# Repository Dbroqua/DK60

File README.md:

# Projet déplacé vers [framagit](https://framagit.org/mechkeyboards/DK60)

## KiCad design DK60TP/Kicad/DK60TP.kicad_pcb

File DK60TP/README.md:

# DK60TP

## About

## Electronic parts
* 1x [ATMEGA32U4](https://www.digikey.com/product-detail/en/microchip-technology/ATMEGA32U4-AUR/ATMEGA32U4-AURCT-ND/3440960)
* 1x [SER3686CT](https://www.digikey.com/product-detail/en/epson/FA-238-16.0000MB-C3/SER3686CT-ND/2403459)
* 2x [22pF capacitors](https://www.digikey.com/product-detail/en/kemet/C0805C220J5GACTU/399-1113-1-ND/411388)
* 9x [0.1uF capacitors](https://www.digikey.com/product-detail/en/yageo/CC0805ZRY5V9BB104/311-1361-1-ND/2103145)
* 1x [4.7uF capacitor](https://www.digikey.com/product-detail/en/murata-electronics-north-america/GRM21BR61E475KA12L/490-3335-1-ND/702876)
* 1x [1uF capacitor](https://www.digikey.com/product-detail/en/yageo/CC0805KKX7R7BB105/311-1365-1-ND/2103149)
* 1x [2.2uF capacitor](https://www.digikey.com/product-detail/en/yageo/CC0805KKX7R7BB225/311-1881-1-ND/5195783)
* 2x [10uF capacitor](https://www.digikey.com/product-detail/en/yageo/CC1206KKX7R7BB106/311-1956-1-ND/5195858)
* 62x [1N4148WTPMSCT](https://www.digikey.com/product-detail/en/micro-commercial-co/1N4148W-TP/1N4148WTPMSCT-ND/717311)
* 5x [WS2812B (only one pack)](http://www.mouser.fr/ProductDetail/Seeed-Studio/110990053/?qs=sGAEpiMZZMtzPgOfznR9QTO1l8g3oIgjmGvsDAmgJrQ%3d)
* 1x [Mini USB connector](https://www.digikey.com/product-detail/en/hirose-electric-co-ltd/UX60SC-MB-5S8/H11589CT-ND/1949225)
* 1x [Inductor 4.7µH](https://www.digikey.com/product-detail/en/bourns-inc/SRN4018-4R7M/SRN4018-4R7MCT-ND/3821520)
* 1x [PLCC 2835](https://www.digikey.com/product-detail/en/osram-opto-semiconductors-inc/LY-T68F-T2V2-35-1-Z/475-2835-1-ND/2176372)
* 1x [Pin header 2x5 angled](https://www.digikey.com/product-detail/en/harwin-inc/M22-2540505/952-2141-ND/3728105)
* 2x [10k Ohm resistors](https://www.digikey.com/product-detail/en/stackpole-electronics-inc/RMCF0805JT10K0/RMCF0805JT10K0CT-ND/1942577)
* 2x [22 Ohm resistors](https://www.digikey.com/product-detail/en/stackpole-electronics-inc/RMCF0805JT22R0/RMCF0805JT22R0CT-ND/1942533)
* 1x [620 Ohm resistor](https://www.digikey.fr/product-detail/fr/stackpole-electronics-inc/RMCF0603JT620R/RMCF0603JT620RCT-ND/1943168)
* 1x [0.5 Ohm resistor](https://www.digikey.com/product-detail/en/yageo/RL0805FR-7W0R5L/311-.5LUCT-ND/3885461)
* 1x [100k Ohm resistor](https://www.digikey.com/product-detail/en/stackpole-electronics-inc/RMCF0805JT100K/RMCF0805JT100KCT-ND/1942592)
* 2x [4.7k Ohm resistor](https://www.digikey.com/product-detail/en/stackpole-electronics-inc/RMCF0805JT4K70/RMCF0805JT4K70CT-ND/1942570)
* 1x [Button](https://www.digikey.com/product-detail/en/e-switch/TL3342F160QG-TR/EG2531CT-ND/379004)
* 1x [PAM2804](https://www.arrow.com/en/products/pam2804aab010/diodes-incorporated)

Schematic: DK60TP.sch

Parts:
C1, C2: 22p; C_0805_HandSoldering
C3, C4, C5, C6: 0.1u; C_0805_HandSoldering
C7: 4.7u; C_0805_HandSoldering
C8: 1u; C_0805_HandSoldering
J1: USB_mini_micro_B; USB_miniB_hirose_5S8
M1, M2, M3, M4: MISC; BreakHoles
P1: CONN_02X04; Molex_PicoBlade_53048-1010_10x1.25mm_Angled
R1, R2: 10K; R_0805_HandSoldering
R3, R4: 22; R_0805_HandSoldering
SW1: SW_PUSH; SW_SPST_TL3342
U0: ATMEGA32U4; TQFP-44_10x10mm_Pitch0.8mm
X1: XTAL_GND; FA-238

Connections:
BACKLIT: U0.12 (PB7/~RTS); also elsewhere on the board
CAPS_LED: U0.1 (PE6/AIN0); also elsewhere on the board
Col0: U0.36 (PF7); also elsewhere on the board
Col1: U0.38 (PF5); also elsewhere on the board
Col2: U0.39 (PF4); also elsewhere on the board
Col3: P1.3, U0.40 (PF1); also elsewhere on the board
Col4: P1.4, U0.30 (PB6); also elsewhere on the board
Col5: P1.5, U0.9 (PB1/SCK); also elsewhere on the board
Col6: U0.26 (T1/PD6); also elsewhere on the board
Col7: U0.11 (PB3/MISO); also elsewhere on the board
Col8: U0.25 (ICP1/PD4); also elsewhere on the board
Col9: U0.28 (PB4); also elsewhere on the board
ColA: U0.21 (PD3/TXD1); also elsewhere on the board
ColB: U0.19 (PD1/INT1); also elsewhere on the board
ColC: U0.18 (PD0/INT0); also elsewhere on the board
ColD: U0.8 (PB0/SS); also elsewhere on the board
D2: P1.7, U0.20 (PD2/RXD1)
D5: P1.6, U0.22 (PD5/XCK1)
DOUT: P1.10; also elsewhere on the board
GND: C1.2, C2.2, C3.2, C4.2, C5.2, C6.2, C7.2, C8.2, J1.5 (GND), J1.6 (SHIELD), P1.2, R2.1, SW1.1, U0.5 (UGnd), U0.15 (GND), U0.23 (GND), U0.35 (GND), U0.43 (GND); also elsewhere on the board
unnamed: C8.1, U0.6 (UCap)
unnamed: J1.2 (D-), R3.2
unnamed: J1.3 (D+), R4.1
unnamed: R2.2, U0.33 (~HWB/PE2)
unnamed: R3.1, U0.3 (D-)
unnamed: R4.2, U0.4 (D+)
RESET: R1.2, SW1.2, U0.13 (~RESET)
RGB: U0.27 (T0/PD7); also elsewhere on the board
Row0: U0.37 (PF6); also elsewhere on the board
Row1: U0.31 (PC6); also elsewhere on the board
Row2: U0.29 (PB5); also elsewhere on the board
Row3: U0.10 (PB2/MOSI); also elsewhere on the board
Row4: P1.8, U0.32 (PC7); also elsewhere on the board
VCC: C3.1, C4.1, C5.1, C6.1, C7.1, J1.1 (VUSB), P1.1, R1.1, U0.2 (UVcc), U0.7 (VBus), U0.14 (VCC), U0.24 (AVCC), U0.34 (VCC), U0.44 (AVCC); also elsewhere on the board
XTAL1: C1.1, U0.16 (XTAL1), X1.1
XTAL2: C2.1, U0.17 (XTAL2), X1.2

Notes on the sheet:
External sheets
Power decoupling
Reset
Clock
µControler
Split PCB holes
Trackpoint connector

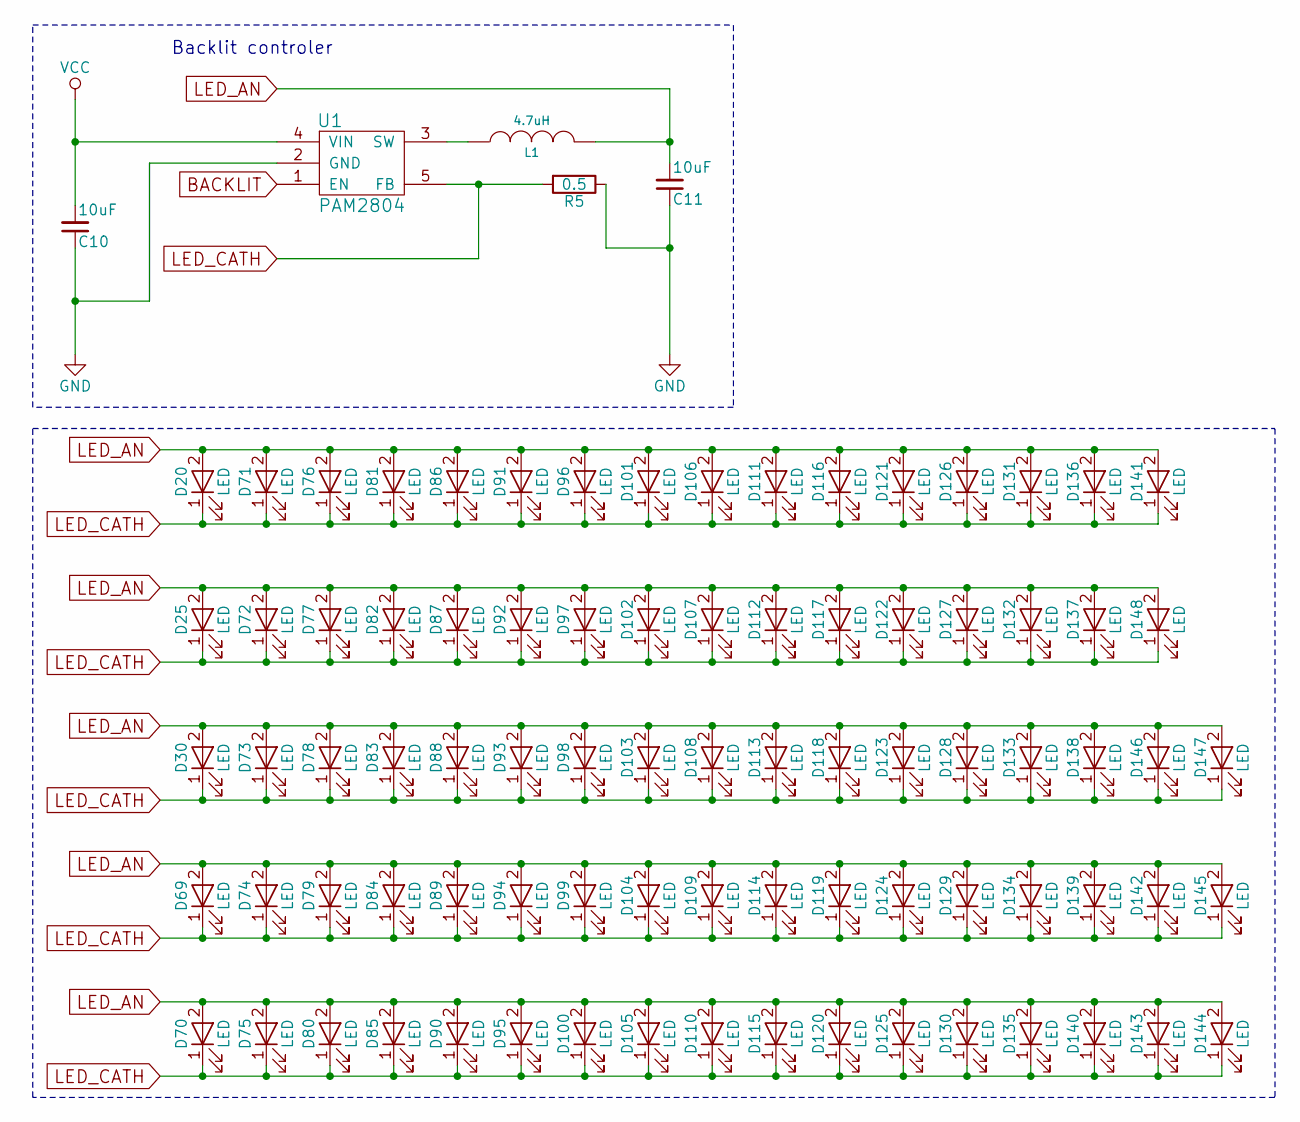
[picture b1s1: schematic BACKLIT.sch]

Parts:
C10, C11: 10uF; C_0805_HandSoldering
D20, D25, D30, D69, D70, D71, D72, D73, D74, D75, D76, D77, D78, D79, D80, D81, D82, D83, D84, D85, D86, D87, D88, D89, D90, D91, D92, D93, D94, D95, D96, D97, D98, D99, D100, D101, D102, D103, D104, D105, D106, D107, D108, D109, D110, D111, D112, D113, D114, D115, D116, D117, D118, D119, D120, D121, D122, D123, D124, D125, D126, D127, D128, D129, D130, D131, D132, D133, D134, D135, D136, D137, D138, D139, D140, D141, D142, D143, D144, D145, D146, D147, D148: LED; LED_TH_BIVAR
L1: 4.7uH; Inductor_Bourn_4mmx4mm
R5: 0.5; R_0805_HandSoldering
U1: PAM2804; SOT-23-5

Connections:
BACKLIT: U1.1 (EN); also elsewhere on the board
GND: C10.1, C11.1, R5.1, U1.2 (GND); also elsewhere on the board
LED_AN: C11.2, D20.2 (A), D25.2 (A), D30.2 (A), D69.2 (A), D70.2 (A), D71.2 (A), D72.2 (A), D73.2 (A), D74.2 (A), D75.2 (A), D76.2 (A), D77.2 (A), D78.2 (A), D79.2 (A), D80.2 (A), D81.2 (A), D82.2 (A), D83.2 (A), D84.2 (A), D85.2 (A), D86.2 (A), D87.2 (A), D88.2 (A), D89.2 (A), D90.2 (A), D91.2 (A), D92.2 (A), D93.2 (A), D94.2 (A), D95.2 (A), D96.2 (A), D97.2 (A), D98.2 (A), D99.2 (A), D100.2 (A), D101.2 (A), D102.2 (A), D103.2 (A), D104.2 (A), D105.2 (A), D106.2 (A), D107.2 (A), D108.2 (A), D109.2 (A), D110.2 (A), D111.2 (A), D112.2 (A), D113.2 (A), D114.2 (A), D115.2 (A), D116.2 (A), D117.2 (A), D118.2 (A), D119.2 (A), D120.2 (A), D121.2 (A), D122.2 (A), D123.2 (A), D124.2 (A), D125.2 (A), D126.2 (A), D127.2 (A), D128.2 (A), D129.2 (A), D130.2 (A), D131.2 (A), D132.2 (A), D133.2 (A), D134.2 (A), D135.2 (A), D136.2 (A), D137.2 (A), D138.2 (A), D139.2 (A), D140.2 (A), D141.2 (A), D142.2 (A), D143.2 (A), D144.2 (A), D145.2 (A), D146.2 (A), D147.2 (A), D148.2 (A), L1.2
LED_CATH: D20.1 (K), D25.1 (K), D30.1 (K), D69.1 (K), D70.1 (K), D71.1 (K), D72.1 (K), D73.1 (K), D74.1 (K), D75.1 (K), D76.1 (K), D77.1 (K), D78.1 (K), D79.1 (K), D80.1 (K), D81.1 (K), D82.1 (K), D83.1 (K), D84.1 (K), D85.1 (K), D86.1 (K), D87.1 (K), D88.1 (K), D89.1 (K), D90.1 (K), D91.1 (K), D92.1 (K), D93.1 (K), D94.1 (K), D95.1 (K), D96.1 (K), D97.1 (K), D98.1 (K), D99.1 (K), D100.1 (K), D101.1 (K), D102.1 (K), D103.1 (K), D104.1 (K), D105.1 (K), D106.1 (K), D107.1 (K), D108.1 (K), D109.1 (K), D110.1 (K), D111.1 (K), D112.1 (K), D113.1 (K), D114.1 (K), D115.1 (K), D116.1 (K), D117.1 (K), D118.1 (K), D119.1 (K), D120.1 (K), D121.1 (K), D122.1 (K), D123.1 (K), D124.1 (K), D125.1 (K), D126.1 (K), D127.1 (K), D128.1 (K), D129.1 (K), D130.1 (K), D131.1 (K), D132.1 (K), D133.1 (K), D134.1 (K), D135.1 (K), D136.1 (K), D137.1 (K), D138.1 (K), D139.1 (K), D140.1 (K), D141.1 (K), D142.1 (K), D143.1 (K), D144.1 (K), D145.1 (K), D146.1 (K), D147.1 (K), D148.1 (K), R5.2, U1.5 (FB)
unnamed: L1.1, U1.3 (SW)
VCC: C10.2, U1.4 (VIN); also elsewhere on the board

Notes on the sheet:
Backlit controler

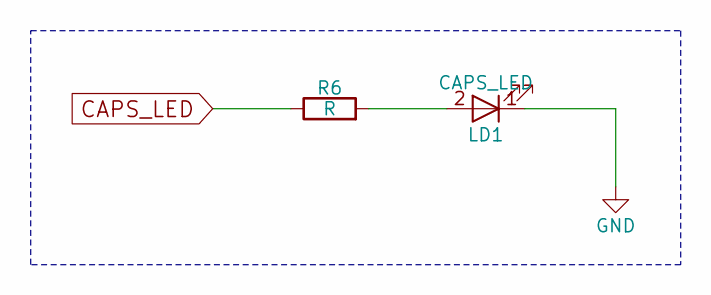
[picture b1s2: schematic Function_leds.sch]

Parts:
LD1: CAPS_LED; LED_PLCC_2835
R6: R; R_0805_HandSoldering

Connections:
CAPS_LED: R6.1; also elsewhere on the board
GND: LD1.1 (K); also elsewhere on the board
unnamed: LD1.2 (A), R6.2

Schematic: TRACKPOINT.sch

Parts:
C9: 2.2u; C_0805_HandSoldering
C17, C18, C19: 0.1u; C_0805_HandSoldering
D154, D155, D156: WS2812B
DM34, DM44, DM54: D; D_SOD123
KM340: LMB; Mx_100
KM341, KM541: KEYSW; Mx_125
KM440: MMB; Mx_100
KM540: KEYSW; Mx_100
P2: MAIN_BOARD; Molex_PicoBlade_53048-1010_10x1.25mm_Angled
P3: TRACKPOINT; Molex_PicoBlade_53048-0510_05x1.25mm_Angled
R7, R8: 4.7K; R_0805_HandSoldering
R9: 100K; R_0805_HandSoldering

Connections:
/TRACKPOINT/Col3: KM340.1, KM341.1, P2.3
/TRACKPOINT/Col4: KM440.1, P2.4
/TRACKPOINT/Col5: KM540.1, KM541.1, P2.5
/TRACKPOINT/D2: P2.7, P3.3, R8.2
/TRACKPOINT/D5: P2.6, P3.5, R7.2
/TRACKPOINT/RGB: D154.4 (DIN), P2.10
/TRACKPOINT/Row4: DM34.1 (K), DM44.1 (K), DM54.1 (K), P2.8
GND: C17.2, C18.2, C19.2, D154.3 (VSS), D155.3 (VSS), D156.3 (VSS), P2.2, P3.2, R9.2; also elsewhere on the board
unnamed: C9.1, P3.4, R9.1
unnamed: D154.2 (DOUT), D155.4 (DIN)
unnamed: D155.2 (DOUT), D156.4 (DIN)
unnamed: DM34.2 (A), KM340.2, KM341.2
unnamed: DM44.2 (A), KM440.2
unnamed: DM54.2 (A), KM540.2, KM541.2
VCC: C9.2, C17.1, C18.1, C19.1, D154.1 (VDD), D155.1 (VDD), D156.1 (VDD), P2.1, P3.1, R7.1, R8.1; also elsewhere on the board

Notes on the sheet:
Connector
Buttons
Trackpoint

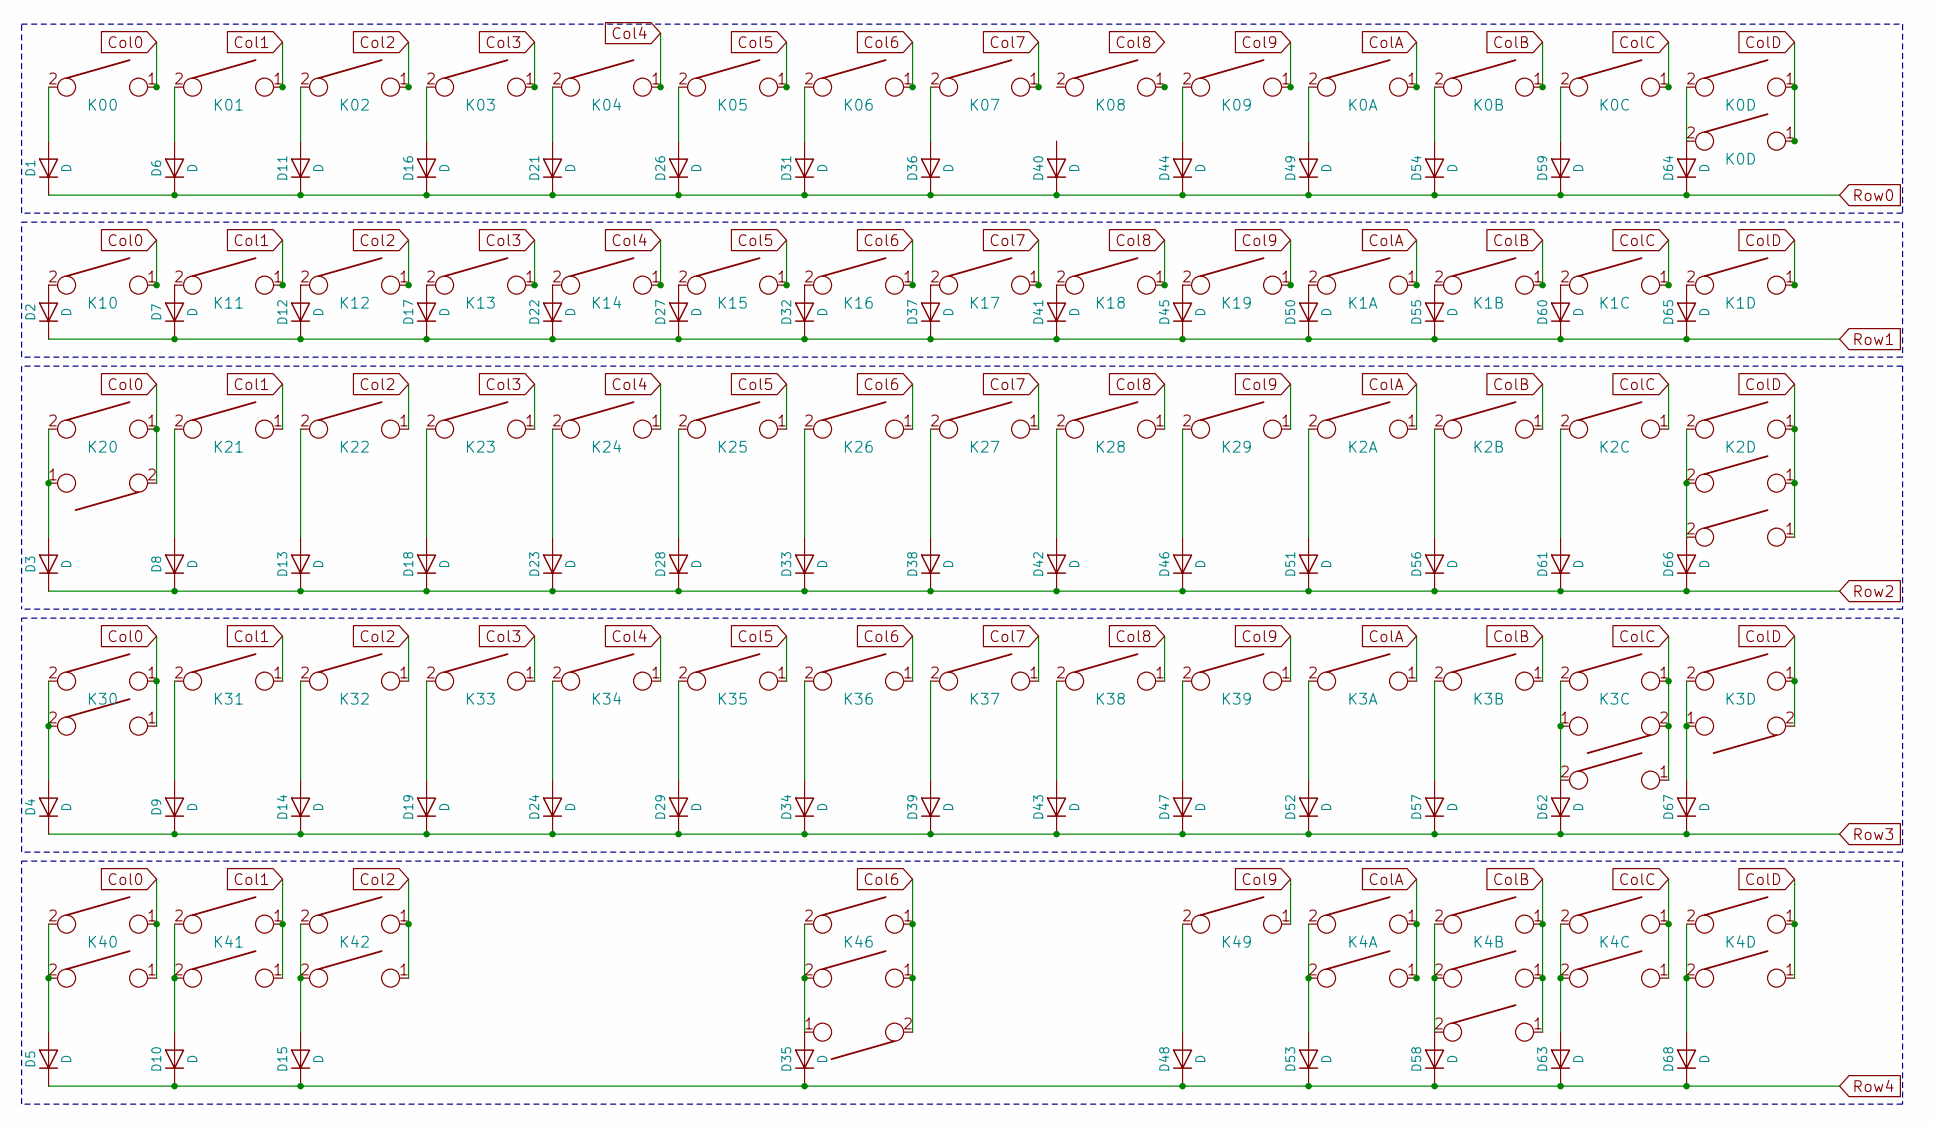
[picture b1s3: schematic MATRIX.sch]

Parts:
D1, D2, D3, D4, D5, D6, D7, D8, D9, D10, D11, D12, D13, D14, D15, D16, D17, D18, D19, D21, D22, D23, D24, D26, D27, D28, D29, D31, D32, D33, D34, D35, D36, D37, D38, D39, D40, D41, D42, D43, D44, D45, D46, D47, D48, D49, D50, D51, D52, D53, D54, D55, D56, D57, D58, D59, D60, D61, D62, D63, D64, D65, D66, D67, D68: D; D_SOD123
K1: K00; Mx_100
K2: K10; Mx_150
K3: K20; Mx_175
K4: K20; Mx_175_STEPPED
K5: K30; Mx_225
K6: K30; Mx_125
K7: K40; Mx_125
K8: K40; Mx_150
K9: K01; Mx_100
K10: K11; Mx_100
K11: K21; Mx_100
K12: K31; Mx_100
K13: K41; Mx_125
K14: K41; Mx_100
K15: K02; Mx_100
K16: K12; Mx_100
K17: K22; Mx_100
K18: K32; Mx_100
K19: K42; Mx_125
K20: K42; Mx_150
K21: K03; Mx_100
K22: K13; Mx_100
K23: K23; Mx_100
K24: K33; Mx_100
K25: K2D; Mx_125
K26: K3D; Mx_175
K27: K04; Mx_100
K28: K14; Mx_100
K29: K24; Mx_100
K30: K34; Mx_100
K31: K3C; Mx_100
K32: K05; Mx_100
K33: K15; Mx_100
K34: K25; Mx_100
K35: K35; Mx_100
K38: K06; Mx_100
K39: K16; Mx_100
K40: K26; Mx_100
K41: K36; Mx_100
K42: K46; Mx_600
K44: K46; Mx_625
K45: K46; Mx_700
K46: K07; Mx_100
K47: K17; Mx_100
K48: K27; Mx_100
K49: K37; Mx_100
K50: K08; Mx_100
K51: K18; Mx_100
K52: K28; Mx_100
K53: K38; Mx_100
K54: K09; Mx_100
K55: K19; Mx_100
K56: K29; Mx_100
K57: K39; Mx_100
K58: K49; Mx_100
K59: K0A; Mx_100
K60: K1A; Mx_100
K61: K2A; Mx_100
K62: K3A; Mx_100
K63: K4A; Mx_125
K64: K4A; Mx_150
K65: K0B; Mx_100
K66: K1B; Mx_100
K67: K2B; Mx_100
K68: K3B; Mx_100
K69: K4B; Mx_100
K70: K4B; Mx_125
K71: K4B; Mx_150
K72: K0C; Mx_100
K73: K1C; Mx_100
K74: K2C; Mx_100
K75: K3C; Mx_275
K76: K4C; Mx_100
K77: K4C; Mx_125
K78: K0D; Mx_100
K79: K0D; Mx_200
K80: K1D; Mx_150
K81: K2D; Mx_225
K82: K2D; Mx_200
K83: K3D; Mx_100
K84: K3C; Mx_175
K85: K4D; Mx_125
K86: K4D; Mx_150

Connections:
Col0: K1.1, K2.1, K3.1, K4.2, K5.1, K6.1, K7.1, K8.1; also elsewhere on the board
Col1: K9.1, K10.1, K11.1, K12.1, K13.1, K14.1; also elsewhere on the board
Col2: K15.1, K16.1, K17.1, K18.1, K19.1, K20.1; also elsewhere on the board
Col3: K21.1, K22.1, K23.1, K24.1; also elsewhere on the board
Col4: K27.1, K28.1, K29.1, K30.1; also elsewhere on the board
Col5: K32.1, K33.1, K34.1, K35.1; also elsewhere on the board
Col6: K38.1, K39.1, K40.1, K41.1, K42.1, K44.1, K45.2; also elsewhere on the board
Col7: K46.1, K47.1, K48.1, K49.1; also elsewhere on the board
Col8: K51.1, K52.1, K53.1; also elsewhere on the board
Col9: K54.1, K55.1, K56.1, K57.1, K58.1; also elsewhere on the board
ColA: K59.1, K60.1, K61.1, K62.1, K63.1, K64.1; also elsewhere on the board
ColB: K65.1, K66.1, K67.1, K68.1, K69.1, K70.1, K71.1; also elsewhere on the board
ColC: K31.2, K72.1, K73.1, K74.1, K75.1, K76.1, K77.1, K84.1; also elsewhere on the board
ColD: K25.1, K26.2, K78.1, K79.1, K80.1, K81.1, K82.1, K83.1, K85.1, K86.1; also elsewhere on the board
unnamed: D1.2 (A), K1.2
unnamed: D2.2 (A), K2.2
unnamed: D3.2 (A), K3.2, K4.1
unnamed: D4.2 (A), K5.2, K6.2
unnamed: D5.2 (A), K7.2, K8.2
unnamed: D6.2 (A), K9.2
unnamed: D7.2 (A), K10.2
unnamed: D8.2 (A), K11.2
unnamed: D9.2 (A), K12.2
unnamed: D10.2 (A), K13.2, K14.2
unnamed: D11.2 (A), K15.2
unnamed: D12.2 (A), K16.2
unnamed: D13.2 (A), K17.2
unnamed: D14.2 (A), K18.2
unnamed: D15.2 (A), K19.2, K20.2
unnamed: D16.2 (A), K21.2
unnamed: D17.2 (A), K22.2
unnamed: D18.2 (A), K23.2
unnamed: D19.2 (A), K24.2
unnamed: D21.2 (A), K27.2
unnamed: D22.2 (A), K28.2
unnamed: D23.2 (A), K29.2
unnamed: D24.2 (A), K30.2
unnamed: D26.2 (A), K32.2
unnamed: D27.2 (A), K33.2
unnamed: D28.2 (A), K34.2
unnamed: D29.2 (A), K35.2
unnamed: D31.2 (A), K38.2
unnamed: D32.2 (A), K39.2
unnamed: D33.2 (A), K40.2
unnamed: D34.2 (A), K41.2
unnamed: D35.2 (A), K42.2, K44.2, K45.1
unnamed: D36.2 (A), K46.2
unnamed: D37.2 (A), K47.2
unnamed: D38.2 (A), K48.2
unnamed: D39.2 (A), K49.2
unnamed: D41.2 (A), K51.2
unnamed: D42.2 (A), K52.2
unnamed: D43.2 (A), K53.2
unnamed: D44.2 (A), K54.2
unnamed: D45.2 (A), K55.2
unnamed: D46.2 (A), K56.2
unnamed: D47.2 (A), K57.2
unnamed: D48.2 (A), K58.2
unnamed: D49.2 (A), K59.2
unnamed: D50.2 (A), K60.2
unnamed: D51.2 (A), K61.2
unnamed: D52.2 (A), K62.2
unnamed: D53.2 (A), K63.2, K64.2
unnamed: D54.2 (A), K65.2
unnamed: D55.2 (A), K66.2
unnamed: D56.2 (A), K67.2
unnamed: D57.2 (A), K68.2
unnamed: D58.2 (A), K69.2, K70.2, K71.2
unnamed: D59.2 (A), K72.2
unnamed: D60.2 (A), K73.2
unnamed: D61.2 (A), K74.2
unnamed: D62.2 (A), K31.1, K75.2, K84.2
unnamed: D63.2 (A), K76.2, K77.2
unnamed: D64.2 (A), K78.2, K79.2
unnamed: D65.2 (A), K80.2
unnamed: D66.2 (A), K25.2, K81.2, K82.2
unnamed: D67.2 (A), K26.1, K83.2
unnamed: D68.2 (A), K85.2, K86.2
Row0: D1.1 (K), D6.1 (K), D11.1 (K), D16.1 (K), D21.1 (K), D26.1 (K), D31.1 (K), D36.1 (K), D40.1 (K), D44.1 (K), D49.1 (K), D54.1 (K), D59.1 (K), D64.1 (K); also elsewhere on the board
Row1: D2.1 (K), D7.1 (K), D12.1 (K), D17.1 (K), D22.1 (K), D27.1 (K), D32.1 (K), D37.1 (K), D41.1 (K), D45.1 (K), D50.1 (K), D55.1 (K), D60.1 (K), D65.1 (K); also elsewhere on the board
Row2: D3.1 (K), D8.1 (K), D13.1 (K), D18.1 (K), D23.1 (K), D28.1 (K), D33.1 (K), D38.1 (K), D42.1 (K), D46.1 (K), D51.1 (K), D56.1 (K), D61.1 (K), D66.1 (K); also elsewhere on the board
Row3: D4.1 (K), D9.1 (K), D14.1 (K), D19.1 (K), D24.1 (K), D29.1 (K), D34.1 (K), D39.1 (K), D43.1 (K), D47.1 (K), D52.1 (K), D57.1 (K), D62.1 (K), D67.1 (K); also elsewhere on the board
Row4: D5.1 (K), D10.1 (K), D15.1 (K), D35.1 (K), D48.1 (K), D53.1 (K), D58.1 (K), D63.1 (K), D68.1 (K); also elsewhere on the board

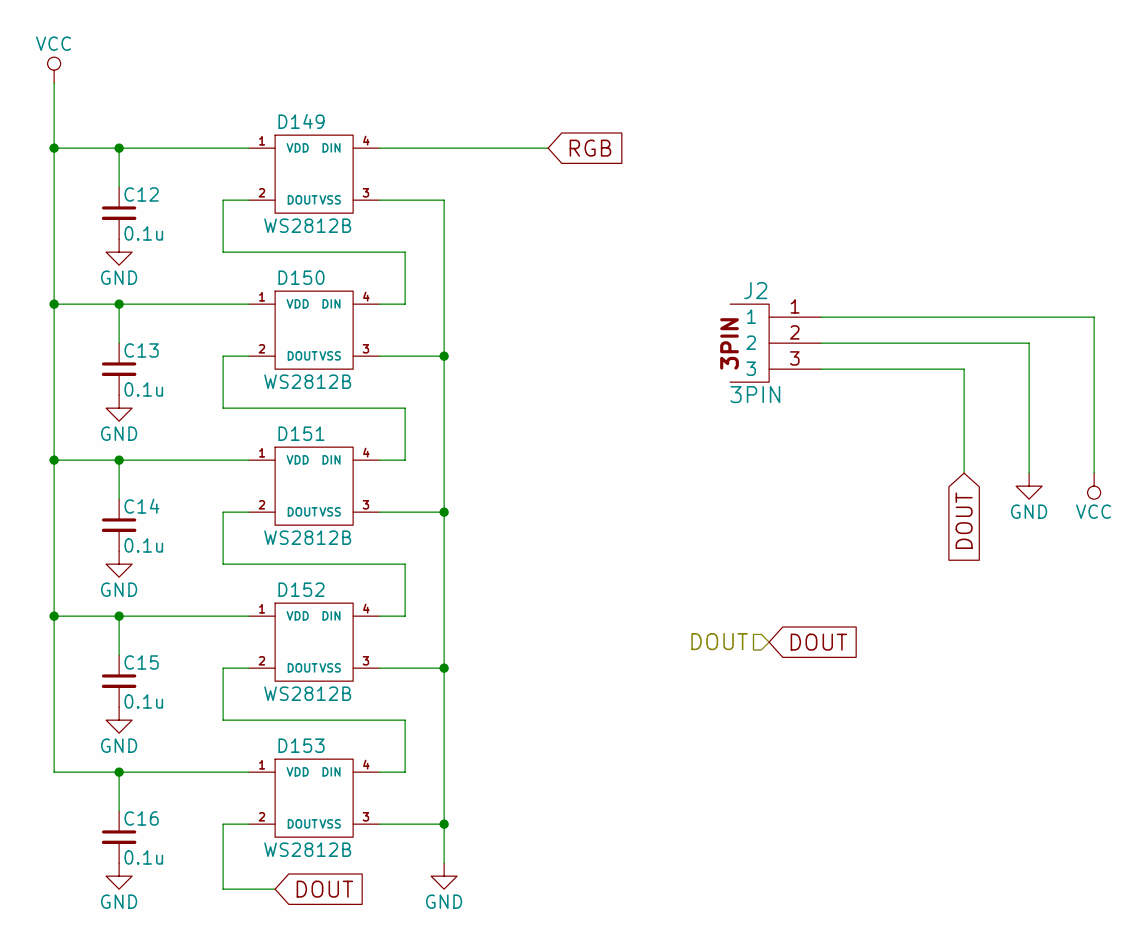
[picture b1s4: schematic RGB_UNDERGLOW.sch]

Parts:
C12, C13, C14, C15, C16: 0.1u; C_0805_HandSoldering
D149, D150, D151, D152, D153: WS2812B
J2: 3PIN; Molex_PicoBlade_53048-0310_03x1.25mm_Angled

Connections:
DOUT: D153.2 (DOUT), J2.3; also elsewhere on the board
GND: C12.2, C13.2, C14.2, C15.2, C16.2, D149.3 (VSS), D150.3 (VSS), D151.3 (VSS), D152.3 (VSS), D153.3 (VSS), J2.2; also elsewhere on the board
unnamed: D149.2 (DOUT), D150.4 (DIN)
unnamed: D150.2 (DOUT), D151.4 (DIN)
unnamed: D151.2 (DOUT), D152.4 (DIN)
unnamed: D152.2 (DOUT), D153.4 (DIN)
RGB: D149.4 (DIN); also elsewhere on the board
VCC: C12.1, C13.1, C14.1, C15.1, C16.1, D149.1 (VDD), D150.1 (VDD), D151.1 (VDD), D152.1 (VDD), D153.1 (VDD), J2.1; also elsewhere on the board

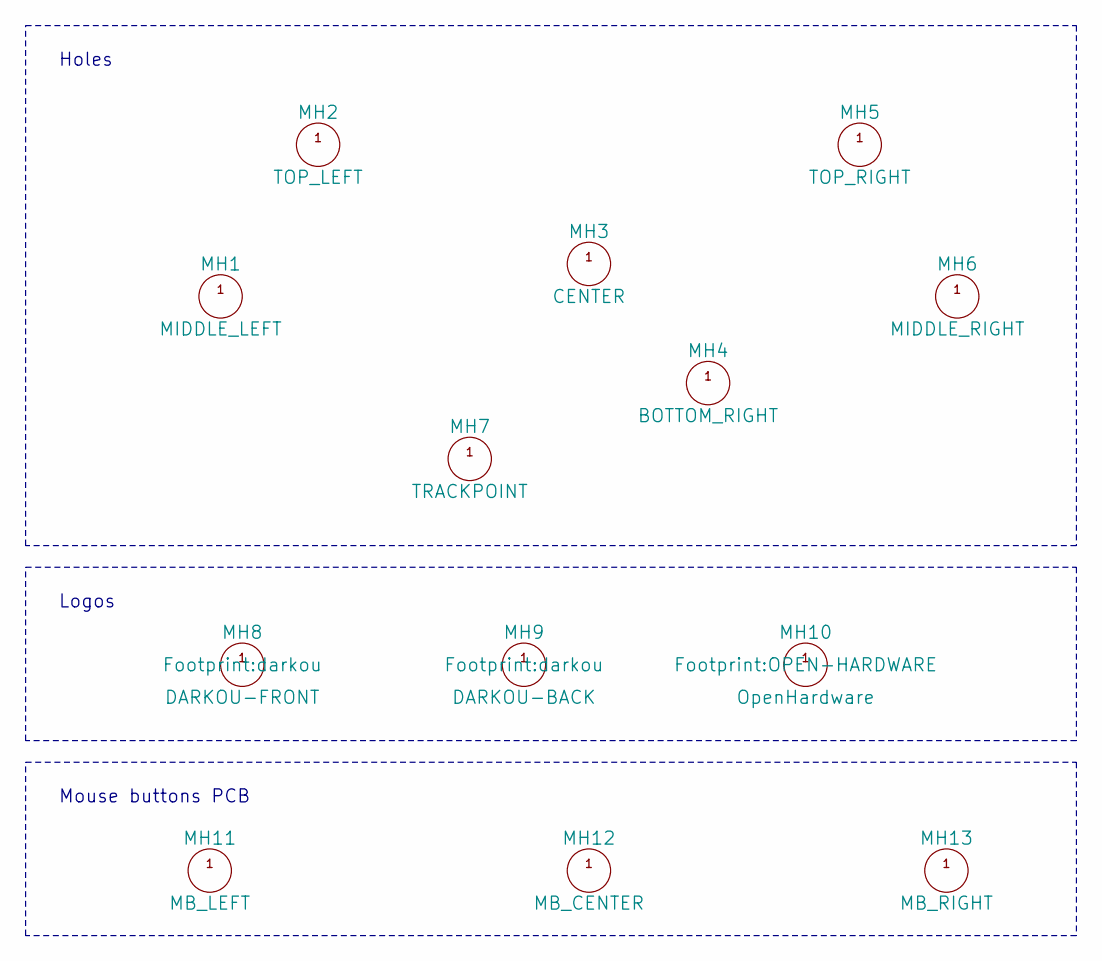
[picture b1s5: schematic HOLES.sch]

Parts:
MH1: MIDDLE_LEFT; Poker_side_edge_long
MH2: TOP_LEFT; MountingHole_2.5mm_Pad
MH3: CENTER; Poker_oval_hole
MH4: BOTTOM_RIGHT; Poker_oval_hole
MH5: TOP_RIGHT; Poker_oval_hole
MH6: MIDDLE_RIGHT; Poker_side_edge_long
MH7: TRACKPOINT; MountingHole_6mm
MH8: DARKOU-FRONT; darkou
MH9: DARKOU-BACK; darkou
MH10: OpenHardware; OPEN-HARDWARE
MH11: MB_LEFT; Poker_oval_hole
MH12: MB_CENTER; Poker_oval_hole
MH13: MB_RIGHT; Poker_oval_hole

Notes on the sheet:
Holes
Logos
Mouse buttons PCB

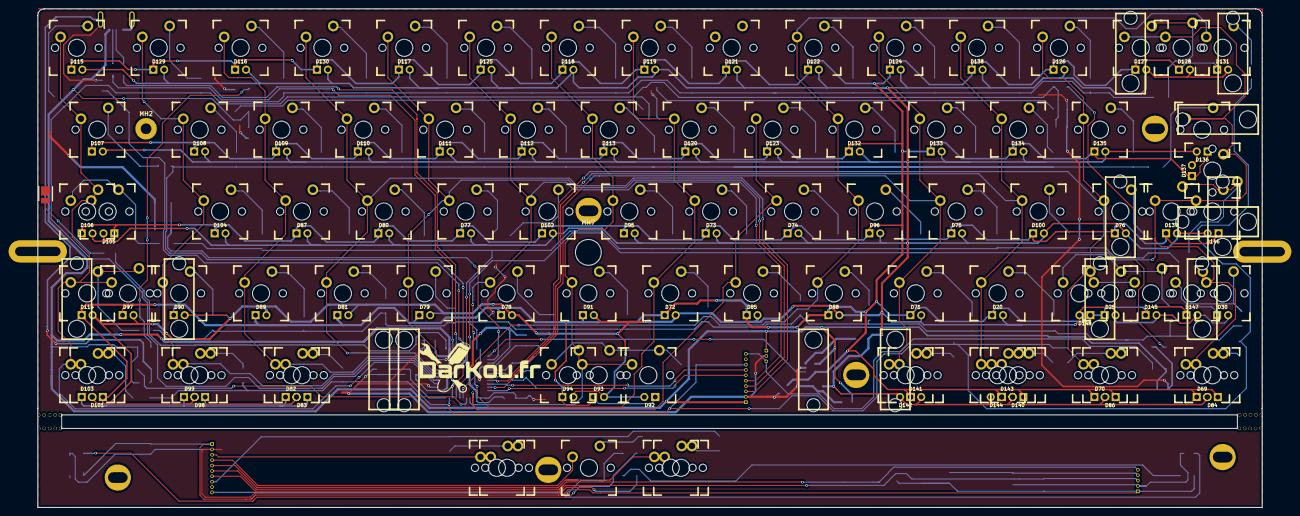
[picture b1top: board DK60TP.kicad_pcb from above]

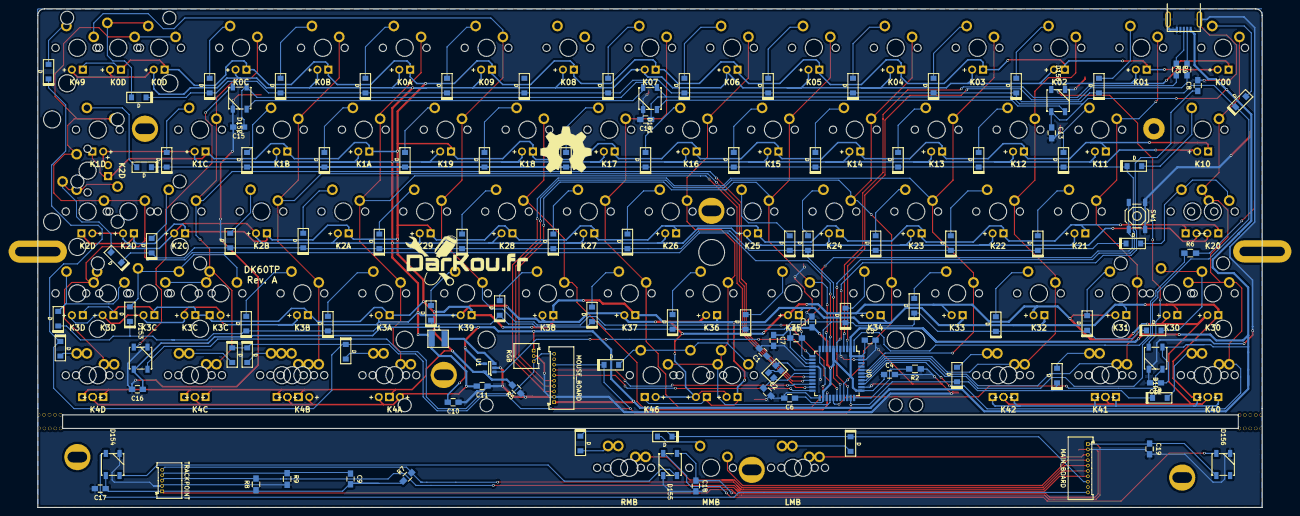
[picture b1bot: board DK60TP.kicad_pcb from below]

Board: 2 copper layers, 285.0 x 116.0 mm, 318 parts (116 on the bottom side), 121 nets.

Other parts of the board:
HOLE_M2.6: VAL**; HOLE_M2.6
MXST: VAL**; MXST
MXST#2, MXST#3, MXST#4, MXST#5, MXST#6, MXST#7, MXST#8, MXST#9, MXST#10, MXST#11, MXST#12, MXST#13, MXST#14: VAL**; MXST

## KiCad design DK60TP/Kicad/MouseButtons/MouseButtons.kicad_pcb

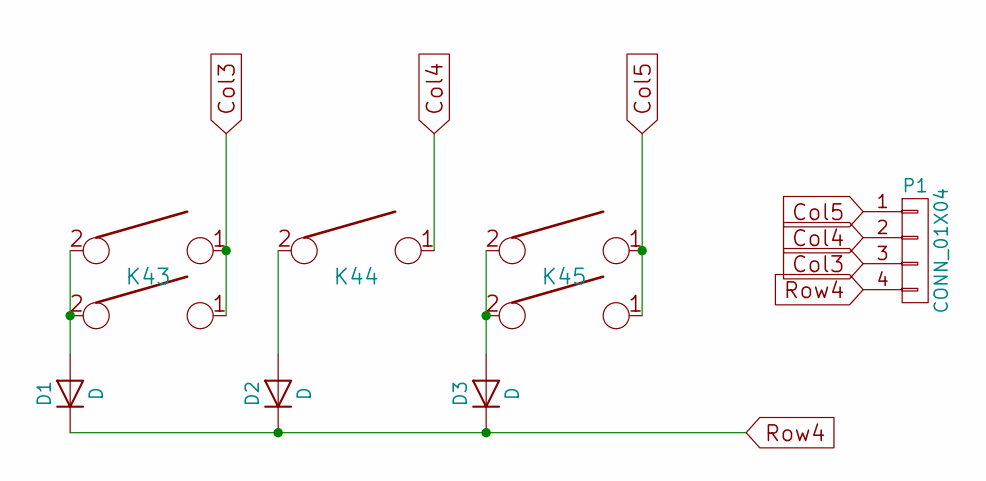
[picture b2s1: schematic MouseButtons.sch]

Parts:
D1, D2, D3: D; D_SOD123
K1: K43; Mx_Alps_100
K2: K43; Mx_Alps_125
K3: K44; Mx_Alps_100
K4: K45; Mx_Alps_100
K5: K45; Mx_Alps_125
P1: CONN_01X04; Pin_Header_Angled_1x04

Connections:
Col3: K1.1, K2.1, P1.3
Col4: K3.1, P1.2
Col5: K4.1, K5.1, P1.1
unnamed: D1.2 (A), K1.2, K2.2
unnamed: D2.2 (A), K3.2
unnamed: D3.2 (A), K4.2, K5.2
Row4: D1.1 (K), D2.1 (K), D3.1 (K), P1.4

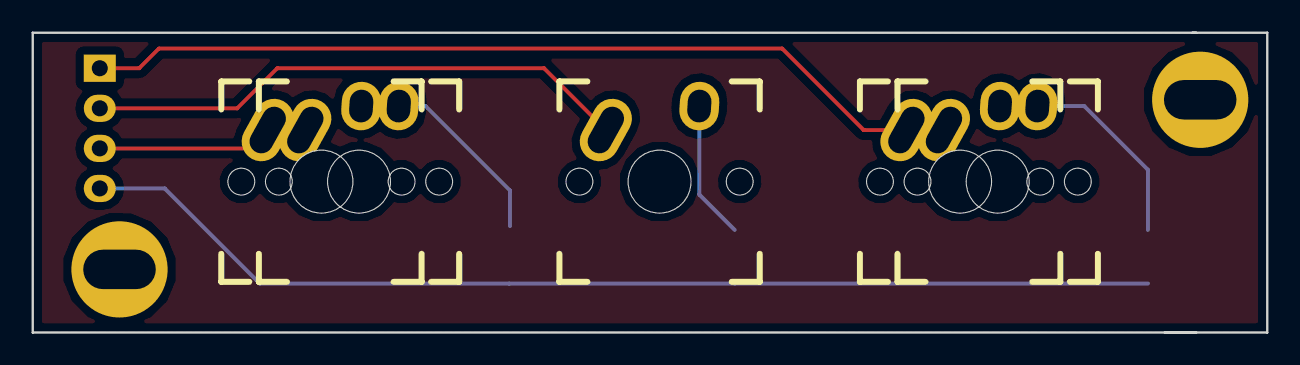
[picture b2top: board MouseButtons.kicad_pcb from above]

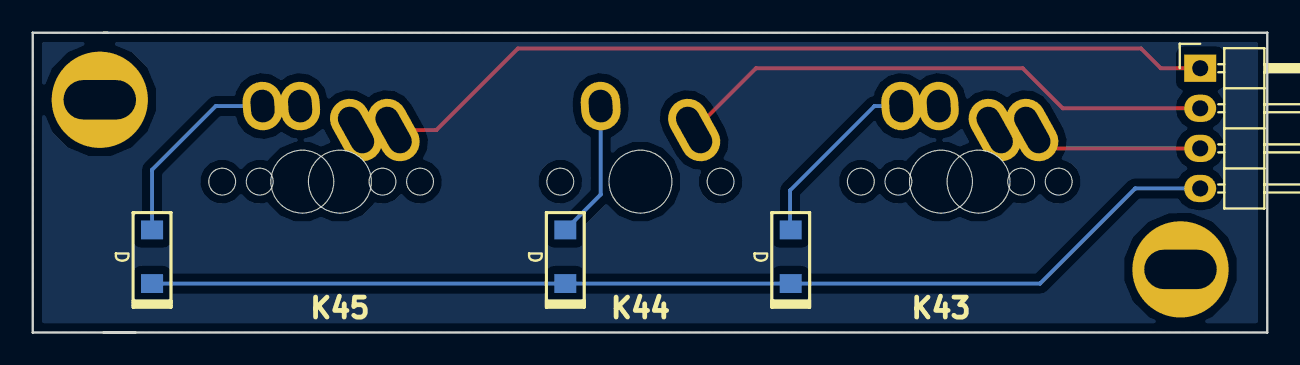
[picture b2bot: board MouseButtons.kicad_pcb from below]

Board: 2 copper layers, 78.2 x 19.0 mm, 11 parts (4 on the bottom side), 7 nets.

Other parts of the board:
Poker_oval_hole: VAL**; Poker_oval_hole
Poker_oval_hole#2: VAL**; Poker_oval_hole
